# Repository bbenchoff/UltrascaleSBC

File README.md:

# UltrascaleSBC

KiCad files for a Zynq UltraScale+ (XCZU3EG) single-board computer.

Write-up: [https://bbenchoff.com/pages/UltrascaleSBC.html](https://bbenchoff.com/pages/UltrascaleSBC.html)

- `Controller.kicad_pro` — KiCad 10 project (schematic, PCB, libraries in `parts/`, 3D models in `3D/`)
- `production/` — Gerbers, BOM, and placement files as ordered from JLCPCB

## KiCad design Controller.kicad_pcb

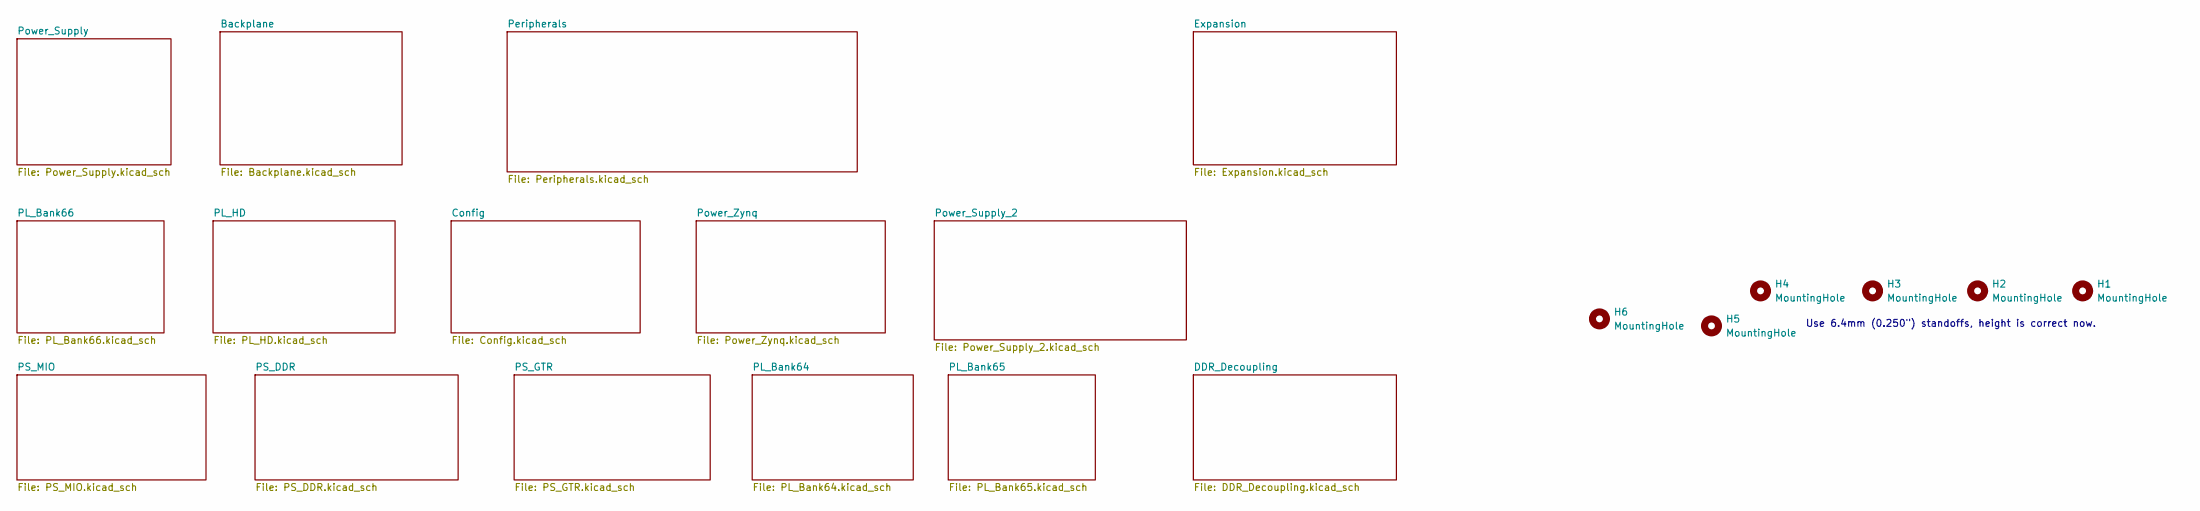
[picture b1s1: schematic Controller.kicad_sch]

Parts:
H1, H2, H3, H4, H5, H6: MountingHole; MountingHole_3.7mm

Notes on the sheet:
Use 6.4mm (0.250") standoffs, height is correct now.

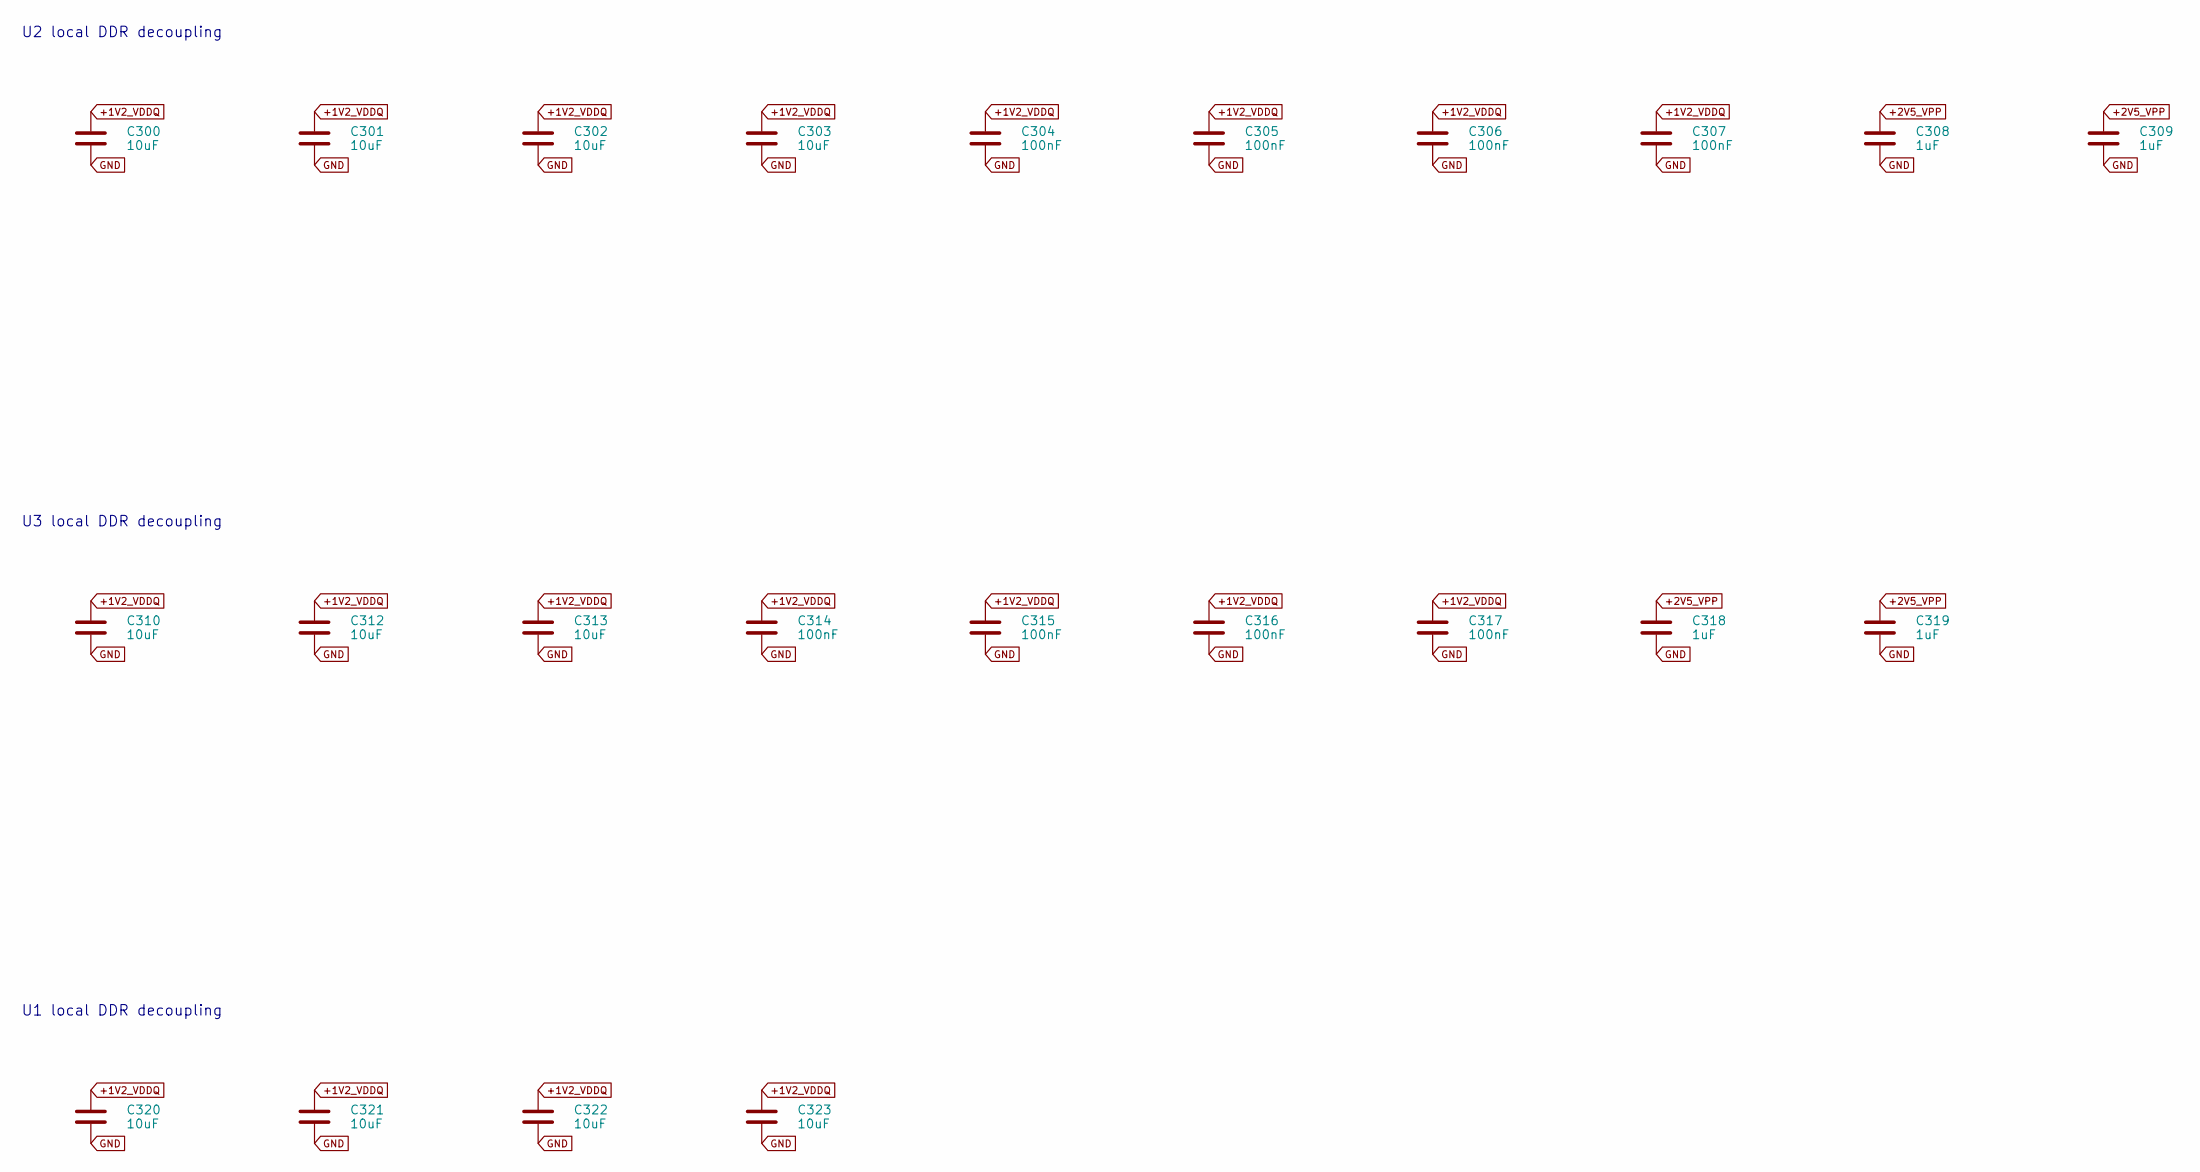
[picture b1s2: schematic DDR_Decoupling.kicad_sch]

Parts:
C300, C301, C302, C303, C310, C312, C313, C320, C321, C322, C323: 10uF; C_0402_1005Metric; MPN CL05A106MP8NUB8; LCSC C307415
C304, C305, C306, C307, C314, C315, C316, C317: 100nF; C_0402_1005Metric; MPN CL05B104KO5NNNC; LCSC C1525
C308, C309, C318, C319: 1uF; C_0402_1005Metric; MPN CL05A105KA5NQNC; LCSC C52923

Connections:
+1V2_VDDQ: C300.1, C301.1, C302.1, C303.1, C304.1, C305.1, C306.1, C307.1, C310.1, C312.1, C313.1, C314.1, C315.1, C316.1, C317.1, C320.1, C321.1, C322.1, C323.1; also elsewhere on the board
+2V5_VPP: C308.1, C309.1, C318.1, C319.1; also elsewhere on the board
GND: C300.2, C301.2, C302.2, C303.2, C304.2, C305.2, C306.2, C307.2, C308.2, C309.2, C310.2, C312.2, C313.2, C314.2, C315.2, C316.2, C317.2, C318.2, C319.2, C320.2, C321.2, C322.2, C323.2; also elsewhere on the board

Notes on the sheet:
U3 local DDR decoupling
U2 local DDR decoupling
U1 local DDR decoupling

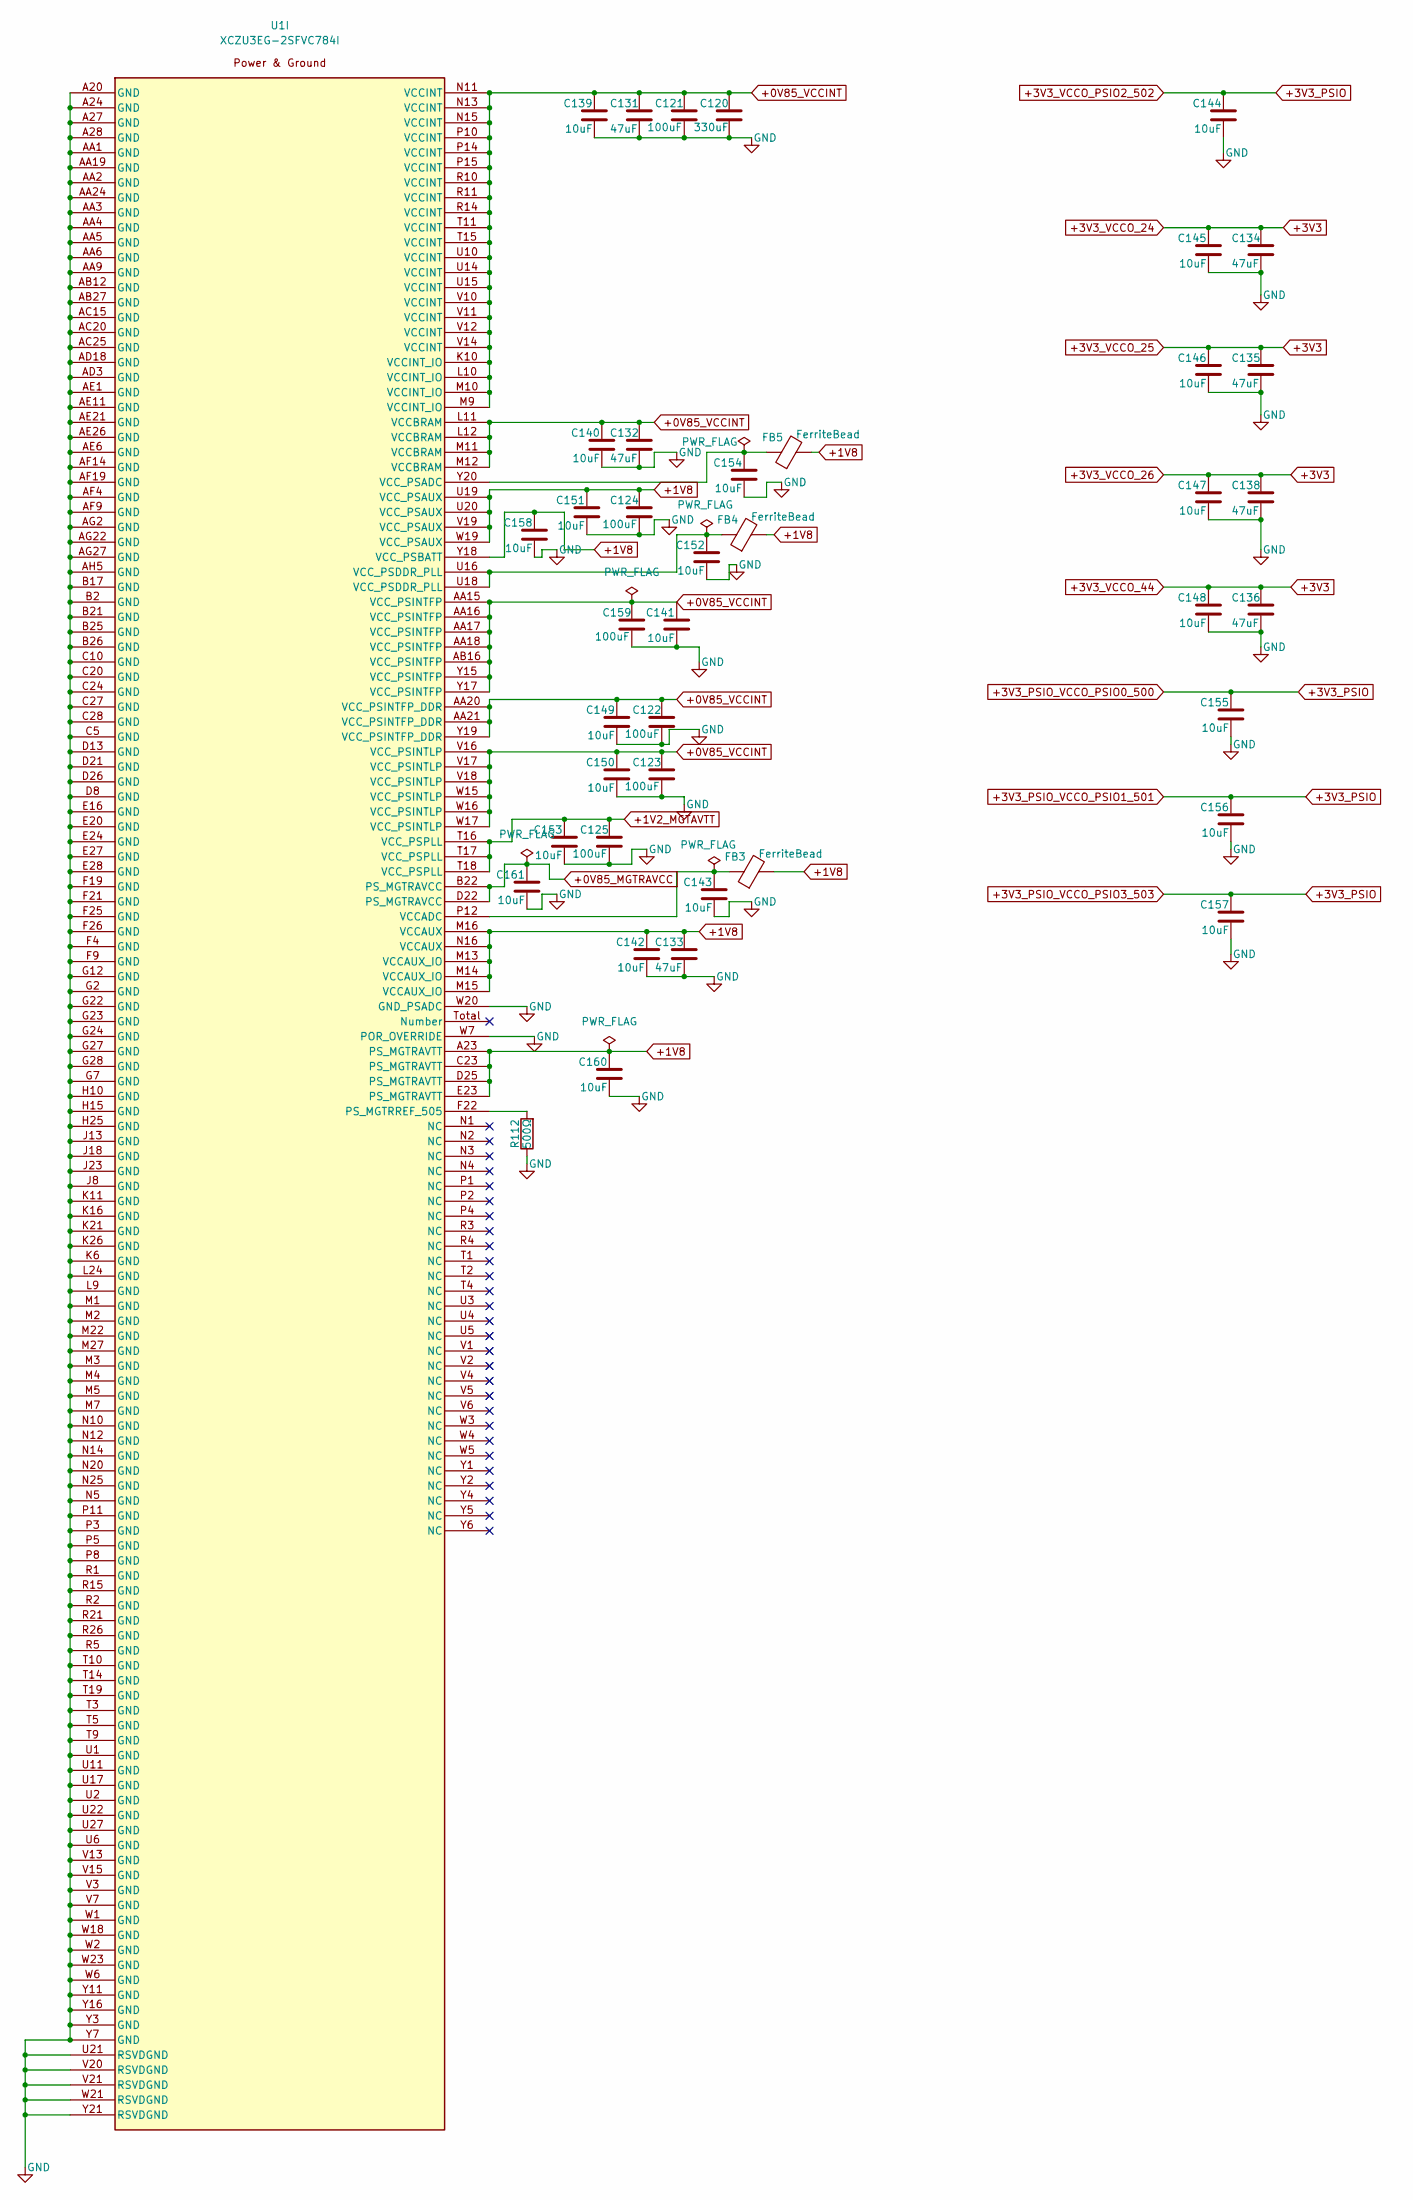
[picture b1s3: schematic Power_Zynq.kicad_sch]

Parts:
C120: 330uF; C_1210_3225Metric; MPN GRM32EC80E337ME05L; LCSC C314600
C121, C122, C123, C124, C125, C159: 100uF; C_0805_2012Metric; MPN GRM21BR60J107ME15L; LCSC C141660
C131, C132, C133, C134, C135, C136, C138: 47uF; C_0603_1608Metric; MPN GRM188R60J476ME15D; LCSC C140782
C139, C140, C141, C142, C143, C144, C145, C146, C147, C148, C149, C150, C151, C152, C153, C154, C155, C156, C157, C158, C160, C161: 10uF; C_0402_1005Metric; MPN CL05A106MP5NUNC; LCSC C315248
FB3, FB4, FB5: FerriteBead; L_0402_1005Metric; MPN BLM15AG601SN1D; LCSC C76884
R112: 500Ω; R_0402_1005Metric; Tolerance 0.1%; MPN CRF0402Q5000BN; LCSC C55205168
U1: XCZU3EG-2SFVC784I; SFVC784_AMD; MPN XCZU3EG-2SFVC784I; LCSC C1550463

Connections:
+0V85_MGTRAVCC: C161.1, U1.B22 (PS_MGTRAVCC), U1.D22 (PS_MGTRAVCC); also elsewhere on the board
+0V85_VCCINT: C120.1, C121.1, C122.1, C123.1, C131.1, C132.1, C139.1, C140.1, C141.1, C149.1, C150.1, C159.1, U1.AA15 (VCC_PSINTFP), U1.AA16 (VCC_PSINTFP), U1.AA17 (VCC_PSINTFP), U1.AA18 (VCC_PSINTFP), U1.AA20 (VCC_PSINTFP_DDR), U1.AA21 (VCC_PSINTFP_DDR), U1.AB16 (VCC_PSINTFP), U1.K10 (VCCINT_IO), U1.L10 (VCCINT_IO), U1.L11 (VCCBRAM), U1.L12 (VCCBRAM), U1.M9 (VCCINT_IO), U1.M10 (VCCINT_IO), U1.M11 (VCCBRAM), U1.M12 (VCCBRAM), U1.N11 (VCCINT), U1.N13 (VCCINT), U1.N15 (VCCINT), U1.P10 (VCCINT), U1.P14 (VCCINT), U1.P15 (VCCINT), U1.R10 (VCCINT), U1.R11 (VCCINT), U1.R14 (VCCINT), U1.T11 (VCCINT), U1.T15 (VCCINT), U1.U10 (VCCINT), U1.U14 (VCCINT), U1.U15 (VCCINT), U1.V10 (VCCINT), U1.V11 (VCCINT), U1.V12 (VCCINT), U1.V14 (VCCINT), U1.V16 (VCC_PSINTLP), U1.V17 (VCC_PSINTLP), U1.V18 (VCC_PSINTLP), U1.W15 (VCC_PSINTLP), U1.W16 (VCC_PSINTLP), U1.W17 (VCC_PSINTLP), U1.Y15 (VCC_PSINTFP), U1.Y17 (VCC_PSINTFP), U1.Y19 (VCC_PSINTFP_DDR); also elsewhere on the board
+1V2_MGTAVTT: C125.1, C153.1, U1.T16 (VCC_PSPLL), U1.T17 (VCC_PSPLL), U1.T18 (VCC_PSPLL); also elsewhere on the board
+1V8: C124.1, C133.1, C142.1, C151.1, C158.1, C160.1, FB3.2, FB4.2, FB5.2, U1.A23 (PS_MGTRAVTT), U1.C23 (PS_MGTRAVTT), U1.D25 (PS_MGTRAVTT), U1.E23 (PS_MGTRAVTT), U1.M13 (VCCAUX_IO), U1.M14 (VCCAUX_IO), U1.M15 (VCCAUX_IO), U1.M16 (VCCAUX), U1.N16 (VCCAUX), U1.U19 (VCC_PSAUX), U1.U20 (VCC_PSAUX), U1.V19 (VCC_PSAUX), U1.W19 (VCC_PSAUX), U1.Y18 (VCC_PSBATT); also elsewhere on the board
+3V3: C134.1, C135.1, C136.1, C138.1, C145.1, C146.1, C147.1, C148.1; also elsewhere on the board
+3V3_PSIO: C144.1, C155.1, C156.1, C157.1; also elsewhere on the board
GND: C120.2, C121.2, C122.2, C123.2, C124.2, C125.2, C131.2, C132.2, C133.2, C134.2, C135.2, C136.2, C138.2, C139.2, C140.2, C141.2, C142.2, C143.2, C144.2, C145.2, C146.2, C147.2, C148.2, C149.2, C150.2, C151.2, C152.2, C153.2, C154.2, C155.2, C156.2, C157.2, C158.2, C159.2, C160.2, C161.2, R112.1, U1.A20 (GND), U1.A24 (GND), U1.A27 (GND), U1.A28 (GND), U1.AA1 (GND), U1.AA2 (GND), U1.AA3 (GND), U1.AA4 (GND), U1.AA5 (GND), U1.AA6 (GND), U1.AA9 (GND), U1.AA19 (GND), U1.AA24 (GND), U1.AB12 (GND), U1.AB27 (GND), U1.AC15 (GND), U1.AC20 (GND), U1.AC25 (GND), U1.AD3 (GND), U1.AD18 (GND), U1.AE1 (GND), U1.AE6 (GND), U1.AE11 (GND), U1.AE21 (GND), U1.AE26 (GND), U1.AF4 (GND), U1.AF9 (GND), U1.AF14 (GND), U1.AF19 (GND), U1.AG2 (GND), U1.AG22 (GND), U1.AG27 (GND), U1.AH5 (GND), U1.B2 (GND), U1.B17 (GND), U1.B21 (GND), U1.B25 (GND), U1.B26 (GND), U1.C5 (GND), U1.C10 (GND), U1.C20 (GND), U1.C24 (GND), U1.C27 (GND), U1.C28 (GND), U1.D8 (GND), U1.D13 (GND), U1.D21 (GND), U1.D26 (GND), U1.E16 (GND), U1.E20 (GND), U1.E24 (GND), U1.E27 (GND), U1.E28 (GND), U1.F4 (GND), U1.F9 (GND), U1.F19 (GND), U1.F21 (GND), U1.F25 (GND), U1.F26 (GND), U1.G2 (GND), U1.G7 (GND), U1.G12 (GND), U1.G22 (GND), U1.G23 (GND), U1.G24 (GND), U1.G27 (GND), U1.G28 (GND), U1.H10 (GND), U1.H15 (GND), U1.H25 (GND), U1.J8 (GND), U1.J13 (GND), U1.J18 (GND), U1.J23 (GND), U1.K6 (GND), U1.K11 (GND), U1.K16 (GND), U1.K21 (GND), U1.K26 (GND), U1.L9 (GND), U1.L24 (GND), U1.M1 (GND), U1.M2 (GND), U1.M3 (GND), U1.M4 (GND), U1.M5 (GND), U1.M7 (GND), U1.M22 (GND), U1.M27 (GND), U1.N5 (GND), U1.N10 (GND), U1.N12 (GND), U1.N14 (GND), U1.N20 (GND), U1.N25 (GND), U1.P3 (GND), U1.P5 (GND), U1.P8 (GND), U1.P11 (GND), U1.R1 (GND), U1.R2 (GND), U1.R5 (GND), U1.R15 (GND), U1.R21 (GND), U1.R26 (GND), U1.T3 (GND), U1.T5 (GND), U1.T9 (GND), U1.T10 (GND), U1.T14 (GND), U1.T19 (GND), U1.U1 (GND), U1.U2 (GND), U1.U6 (GND), U1.U11 (GND), U1.U17 (GND), U1.U21 (RSVDGND), U1.U22 (GND), U1.U27 (GND), U1.V3 (GND), U1.V7 (GND), U1.V13 (GND), U1.V15 (GND), U1.V20 (RSVDGND), U1.V21 (RSVDGND), U1.W1 (GND), U1.W2 (GND), U1.W6 (GND), U1.W7 (POR_OVERRIDE), U1.W18 (GND), U1.W20 (GND_PSADC), U1.W21 (RSVDGND), U1.W23 (GND), U1.Y3 (GND), U1.Y7 (GND), U1.Y11 (GND), U1.Y16 (GND), U1.Y21 (RSVDGND); also elsewhere on the board
unnamed: C152.1, FB4.1, U1.U16 (VCC_PSDDR_PLL), U1.U18 (VCC_PSDDR_PLL)
unnamed: R112.2, U1.F22 (PS_MGTRREF_505)
unnamed: C143.1, FB3.1, U1.P12 (VCCADC)
unnamed: C154.1, FB5.1, U1.Y20 (VCC_PSADC)

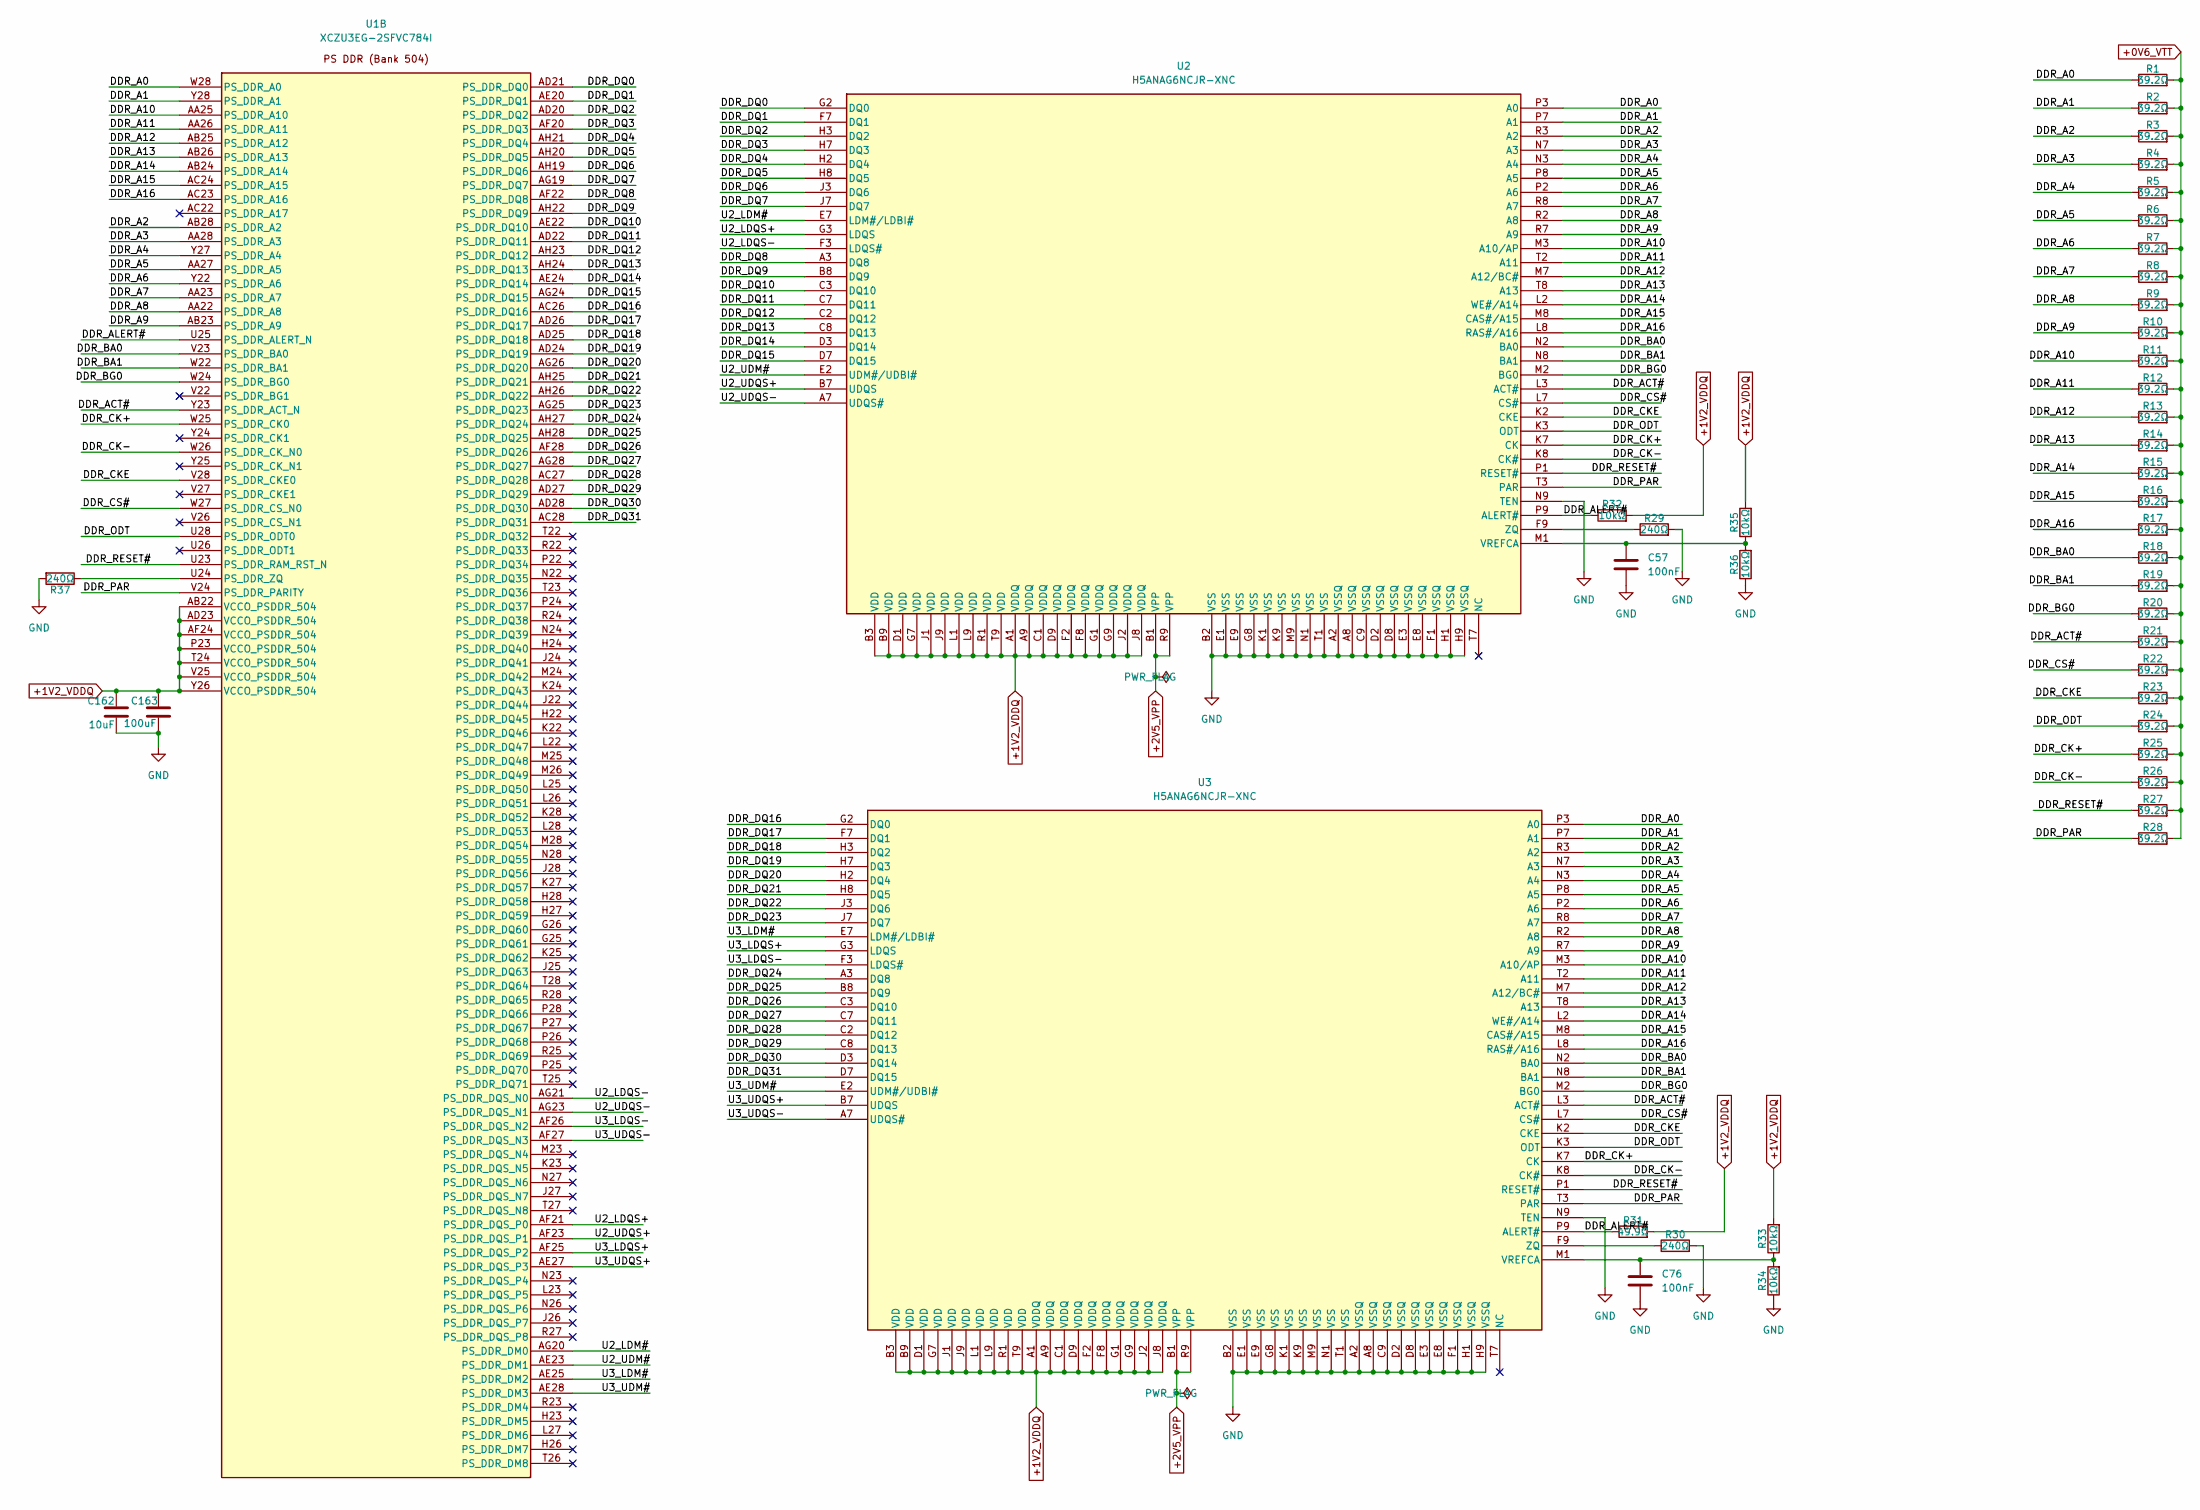
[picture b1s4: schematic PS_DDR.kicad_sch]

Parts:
C57, C76: 100nF; C_0402_1005Metric; MPN CL05B104KO5NNNC; LCSC C1525
C162: 10uF; C_0402_1005Metric; MPN CL05A106MP5NUNC; LCSC C315248
C163: 100uF; C_0805_2012Metric; MPN GRM21BR60J107ME15L; LCSC C141660
R1, R2, R3, R4, R5, R6, R7, R8, R9, R10, R11, R12, R13, R14, R15, R16, R17, R18, R19, R20, R21, R22, R23, R24, R25, R26, R27, R28: 39.2Ω; R_0402_1005Metric; Tolerance 1%; MPN 0402WGF392JTCE; LCSC C45323
R29, R30, R37: 240Ω; R_0402_1005Metric; Tolerance 1%; MPN 0402WGF2400TCE; LCSC C25094
R31: 49.9Ω; R_0402_1005Metric; Tolerance 1%; MPN 0402WGF499JTCE; LCSC C25120
R32, R33, R34, R35, R36: 10kΩ; R_0402_1005Metric; Tolerance 1%; MPN 0402WGF1002TCE; LCSC C25744
U1: XCZU3EG-2SFVC784I; SFVC784_AMD; MPN XCZU3EG-2SFVC784I; LCSC C1550463
U2, U3: H5ANAG6NCJR-XNC; Micron_FBGA-96_7.5x13.5mm_Layout9x16_P0.8mm; MPN H5ANAG6NCJR-XNC; LCSC C2960662

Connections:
+0V6_VTT: R1.2, R2.2, R3.2, R4.2, R5.2, R6.2, R7.2, R8.2, R9.2, R10.2, R11.2, R12.2, R13.2, R14.2, R15.2, R16.2, R17.2, R18.2, R19.2, R20.2, R21.2, R22.2, R23.2, R24.2, R25.2, R26.2, R27.2, R28.2; also elsewhere on the board
+1V2_VDDQ: C162.1, C163.1, R31.2, R32.2, R33.2, R35.2, U1.AB22 (VCCO_PSDDR_504), U1.AD23 (VCCO_PSDDR_504), U1.AF24 (VCCO_PSDDR_504), U1.P23 (VCCO_PSDDR_504), U1.T24 (VCCO_PSDDR_504), U1.V25 (VCCO_PSDDR_504), U1.Y26 (VCCO_PSDDR_504), U2.A1 (VDDQ), U2.A9 (VDDQ), U2.B3 (VDD), U2.B9 (VDD), U2.C1 (VDDQ), U2.D1 (VDD), U2.D9 (VDDQ), U2.F2 (VDDQ), U2.F8 (VDDQ), U2.G1 (VDDQ), U2.G7 (VDD), U2.G9 (VDDQ), U2.J1 (VDD), U2.J2 (VDDQ), U2.J8 (VDDQ), U2.J9 (VDD), U2.L1 (VDD), U2.L9 (VDD), U2.R1 (VDD), U2.T9 (VDD), U3.A1 (VDDQ), U3.A9 (VDDQ), U3.B3 (VDD), U3.B9 (VDD), U3.C1 (VDDQ), U3.D1 (VDD), U3.D9 (VDDQ), U3.F2 (VDDQ), U3.F8 (VDDQ), U3.G1 (VDDQ), U3.G7 (VDD), U3.G9 (VDDQ), U3.J1 (VDD), U3.J2 (VDDQ), U3.J8 (VDDQ), U3.J9 (VDD), U3.L1 (VDD), U3.L9 (VDD), U3.R1 (VDD), U3.T9 (VDD); also elsewhere on the board
+2V5_VPP: U2.B1 (VPP), U2.R9 (VPP), U3.B1 (VPP), U3.R9 (VPP); also elsewhere on the board
/PS_DDR/DDR_A0: R1.1, U1.W28 (PS_DDR_A0), U2.P3 (A0), U3.P3 (A0)
/PS_DDR/DDR_A1: R2.1, U1.Y28 (PS_DDR_A1), U2.P7 (A1), U3.P7 (A1)
/PS_DDR/DDR_A2: R3.1, U1.AB28 (PS_DDR_A2), U2.R3 (A2), U3.R3 (A2)
/PS_DDR/DDR_A3: R4.1, U1.AA28 (PS_DDR_A3), U2.N7 (A3), U3.N7 (A3)
/PS_DDR/DDR_A4: R5.1, U1.Y27 (PS_DDR_A4), U2.N3 (A4), U3.N3 (A4)
/PS_DDR/DDR_A5: R6.1, U1.AA27 (PS_DDR_A5), U2.P8 (A5), U3.P8 (A5)
/PS_DDR/DDR_A6: R7.1, U1.Y22 (PS_DDR_A6), U2.P2 (A6), U3.P2 (A6)
/PS_DDR/DDR_A7: R8.1, U1.AA23 (PS_DDR_A7), U2.R8 (A7), U3.R8 (A7)
/PS_DDR/DDR_A8: R9.1, U1.AA22 (PS_DDR_A8), U2.R2 (A8), U3.R2 (A8)
/PS_DDR/DDR_A9: R10.1, U1.AB23 (PS_DDR_A9), U2.R7 (A9), U3.R7 (A9)
/PS_DDR/DDR_A10: R11.1, U1.AA25 (PS_DDR_A10), U2.M3 (A10/AP), U3.M3 (A10/AP)
/PS_DDR/DDR_A11: R12.1, U1.AA26 (PS_DDR_A11), U2.T2 (A11), U3.T2 (A11)
/PS_DDR/DDR_A12: R13.1, U1.AB25 (PS_DDR_A12), U2.M7 (A12/BC#), U3.M7 (A12/BC#)
/PS_DDR/DDR_A13: R14.1, U1.AB26 (PS_DDR_A13), U2.T8 (A13), U3.T8 (A13)
/PS_DDR/DDR_A14: R15.1, U1.AB24 (PS_DDR_A14), U2.L2 (WE#/A14), U3.L2 (WE#/A14)
/PS_DDR/DDR_A15: R16.1, U1.AC24 (PS_DDR_A15), U2.M8 (CAS#/A15), U3.M8 (CAS#/A15)
/PS_DDR/DDR_A16: R17.1, U1.AC23 (PS_DDR_A16), U2.L8 (RAS#/A16), U3.L8 (RAS#/A16)
/PS_DDR/DDR_ACT#: R21.1, U1.Y23 (PS_DDR_ACT_N), U2.L3 (ACT#), U3.L3 (ACT#)
/PS_DDR/DDR_ALERT#: R31.1, R32.1, U1.U25 (PS_DDR_ALERT_N), U2.P9 (ALERT#), U3.P9 (ALERT#)
/PS_DDR/DDR_BA0: R18.1, U1.V23 (PS_DDR_BA0), U2.N2 (BA0), U3.N2 (BA0)
/PS_DDR/DDR_BA1: R19.1, U1.W22 (PS_DDR_BA1), U2.N8 (BA1), U3.N8 (BA1)
/PS_DDR/DDR_BG0: R20.1, U1.W24 (PS_DDR_BG0), U2.M2 (BG0), U3.M2 (BG0)
/PS_DDR/DDR_CK+: R25.1, U1.W25 (PS_DDR_CK0), U2.K7 (CK), U3.K7 (CK)
/PS_DDR/DDR_CK-: R26.1, U1.W26 (PS_DDR_CK_N0), U2.K8 (CK#), U3.K8 (CK#)
/PS_DDR/DDR_CKE: R23.1, U1.V28 (PS_DDR_CKE0), U2.K2 (CKE), U3.K2 (CKE)
/PS_DDR/DDR_CS#: R22.1, U1.W27 (PS_DDR_CS_N0), U2.L7 (CS#), U3.L7 (CS#)
/PS_DDR/DDR_DQ0: U1.AD21 (PS_DDR_DQ0), U2.G2 (DQ0)
/PS_DDR/DDR_DQ1: U1.AE20 (PS_DDR_DQ1), U2.F7 (DQ1)
/PS_DDR/DDR_DQ2: U1.AD20 (PS_DDR_DQ2), U2.H3 (DQ2)
/PS_DDR/DDR_DQ3: U1.AF20 (PS_DDR_DQ3), U2.H7 (DQ3)
/PS_DDR/DDR_DQ4: U1.AH21 (PS_DDR_DQ4), U2.H2 (DQ4)
/PS_DDR/DDR_DQ5: U1.AH20 (PS_DDR_DQ5), U2.H8 (DQ5)
/PS_DDR/DDR_DQ6: U1.AH19 (PS_DDR_DQ6), U2.J3 (DQ6)
/PS_DDR/DDR_DQ7: U1.AG19 (PS_DDR_DQ7), U2.J7 (DQ7)
/PS_DDR/DDR_DQ8: U1.AF22 (PS_DDR_DQ8), U2.A3 (DQ8)
/PS_DDR/DDR_DQ9: U1.AH22 (PS_DDR_DQ9), U2.B8 (DQ9)
/PS_DDR/DDR_DQ10: U1.AE22 (PS_DDR_DQ10), U2.C3 (DQ10)
/PS_DDR/DDR_DQ11: U1.AD22 (PS_DDR_DQ11), U2.C7 (DQ11)
/PS_DDR/DDR_DQ12: U1.AH23 (PS_DDR_DQ12), U2.C2 (DQ12)
/PS_DDR/DDR_DQ13: U1.AH24 (PS_DDR_DQ13), U2.C8 (DQ13)
/PS_DDR/DDR_DQ14: U1.AE24 (PS_DDR_DQ14), U2.D3 (DQ14)
/PS_DDR/DDR_DQ15: U1.AG24 (PS_DDR_DQ15), U2.D7 (DQ15)
/PS_DDR/DDR_DQ16: U1.AC26 (PS_DDR_DQ16), U3.G2 (DQ0)
/PS_DDR/DDR_DQ17: U1.AD26 (PS_DDR_DQ17), U3.F7 (DQ1)
/PS_DDR/DDR_DQ18: U1.AD25 (PS_DDR_DQ18), U3.H3 (DQ2)
/PS_DDR/DDR_DQ19: U1.AD24 (PS_DDR_DQ19), U3.H7 (DQ3)
/PS_DDR/DDR_DQ20: U1.AG26 (PS_DDR_DQ20), U3.H2 (DQ4)
/PS_DDR/DDR_DQ21: U1.AH25 (PS_DDR_DQ21), U3.H8 (DQ5)
/PS_DDR/DDR_DQ22: U1.AH26 (PS_DDR_DQ22), U3.J3 (DQ6)
/PS_DDR/DDR_DQ23: U1.AG25 (PS_DDR_DQ23), U3.J7 (DQ7)
/PS_DDR/DDR_DQ24: U1.AH27 (PS_DDR_DQ24), U3.A3 (DQ8)
/PS_DDR/DDR_DQ25: U1.AH28 (PS_DDR_DQ25), U3.B8 (DQ9)
/PS_DDR/DDR_DQ26: U1.AF28 (PS_DDR_DQ26), U3.C3 (DQ10)
/PS_DDR/DDR_DQ27: U1.AG28 (PS_DDR_DQ27), U3.C7 (DQ11)
/PS_DDR/DDR_DQ28: U1.AC27 (PS_DDR_DQ28), U3.C2 (DQ12)
/PS_DDR/DDR_DQ29: U1.AD27 (PS_DDR_DQ29), U3.C8 (DQ13)
/PS_DDR/DDR_DQ30: U1.AD28 (PS_DDR_DQ30), U3.D3 (DQ14)
/PS_DDR/DDR_DQ31: U1.AC28 (PS_DDR_DQ31), U3.D7 (DQ15)
/PS_DDR/DDR_ODT: R24.1, U1.U28 (PS_DDR_ODT0), U2.K3 (ODT), U3.K3 (ODT)
/PS_DDR/DDR_PAR: R28.1, U1.V24 (PS_DDR_PARITY), U2.T3 (PAR), U3.T3 (PAR)
/PS_DDR/DDR_RESET#: R27.1, U1.U23 (PS_DDR_RAM_RST_N), U2.P1 (RESET#), U3.P1 (RESET#)
/PS_DDR/U2_LDM#: U1.AG20 (PS_DDR_DM0), U2.E7 (LDM#/LDBI#)
/PS_DDR/U2_LDQS+: U1.AF21 (PS_DDR_DQS_P0), U2.G3 (LDQS)
/PS_DDR/U2_LDQS-: U1.AG21 (PS_DDR_DQS_N0), U2.F3 (LDQS#)
/PS_DDR/U2_UDM#: U1.AE23 (PS_DDR_DM1), U2.E2 (UDM#/UDBI#)
/PS_DDR/U2_UDQS+: U1.AF23 (PS_DDR_DQS_P1), U2.B7 (UDQS)
/PS_DDR/U2_UDQS-: U1.AG23 (PS_DDR_DQS_N1), U2.A7 (UDQS#)
/PS_DDR/U3_LDM#: U1.AE25 (PS_DDR_DM2), U3.E7 (LDM#/LDBI#)
/PS_DDR/U3_LDQS+: U1.AF25 (PS_DDR_DQS_P2), U3.G3 (LDQS)
/PS_DDR/U3_LDQS-: U1.AF26 (PS_DDR_DQS_N2), U3.F3 (LDQS#)
/PS_DDR/U3_UDM#: U1.AE28 (PS_DDR_DM3), U3.E2 (UDM#/UDBI#)
/PS_DDR/U3_UDQS+: U1.AE27 (PS_DDR_DQS_P3), U3.B7 (UDQS)
/PS_DDR/U3_UDQS-: U1.AF27 (PS_DDR_DQS_N3), U3.A7 (UDQS#)
GND: C57.2, C76.2, C162.2, C163.2, R29.2, R30.2, R34.1, R36.1, R37.2, U2.A2 (VSSQ), U2.A8 (VSSQ), U2.B2 (VSS), U2.C9 (VSSQ), U2.D2 (VSSQ), U2.D8 (VSSQ), U2.E1 (VSS), U2.E3 (VSSQ), U2.E8 (VSSQ), U2.E9 (VSS), U2.F1 (VSSQ), U2.G8 (VSS), U2.H1 (VSSQ), U2.H9 (VSSQ), U2.K1 (VSS), U2.K9 (VSS), U2.M9 (VSS), U2.N1 (VSS), U2.N9 (TEN), U2.T1 (VSS), U3.A2 (VSSQ), U3.A8 (VSSQ), U3.B2 (VSS), U3.C9 (VSSQ), U3.D2 (VSSQ), U3.D8 (VSSQ), U3.E1 (VSS), U3.E3 (VSSQ), U3.E8 (VSSQ), U3.E9 (VSS), U3.F1 (VSSQ), U3.G8 (VSS), U3.H1 (VSSQ), U3.H9 (VSSQ), U3.K1 (VSS), U3.K9 (VSS), U3.M9 (VSS), U3.N1 (VSS), U3.N9 (TEN), U3.T1 (VSS); also elsewhere on the board
unnamed: R37.1, U1.U24 (PS_DDR_ZQ)
unnamed: C57.1, R35.1, R36.2, U2.M1 (VREFCA)
unnamed: R29.1, U2.F9 (ZQ)
unnamed: C76.1, R33.1, R34.2, U3.M1 (VREFCA)
unnamed: R30.1, U3.F9 (ZQ)
